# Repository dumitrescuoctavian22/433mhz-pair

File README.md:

# 433mhz-pair
A pair of transmitter and receiver with 4 channels working on 433,92Mhz

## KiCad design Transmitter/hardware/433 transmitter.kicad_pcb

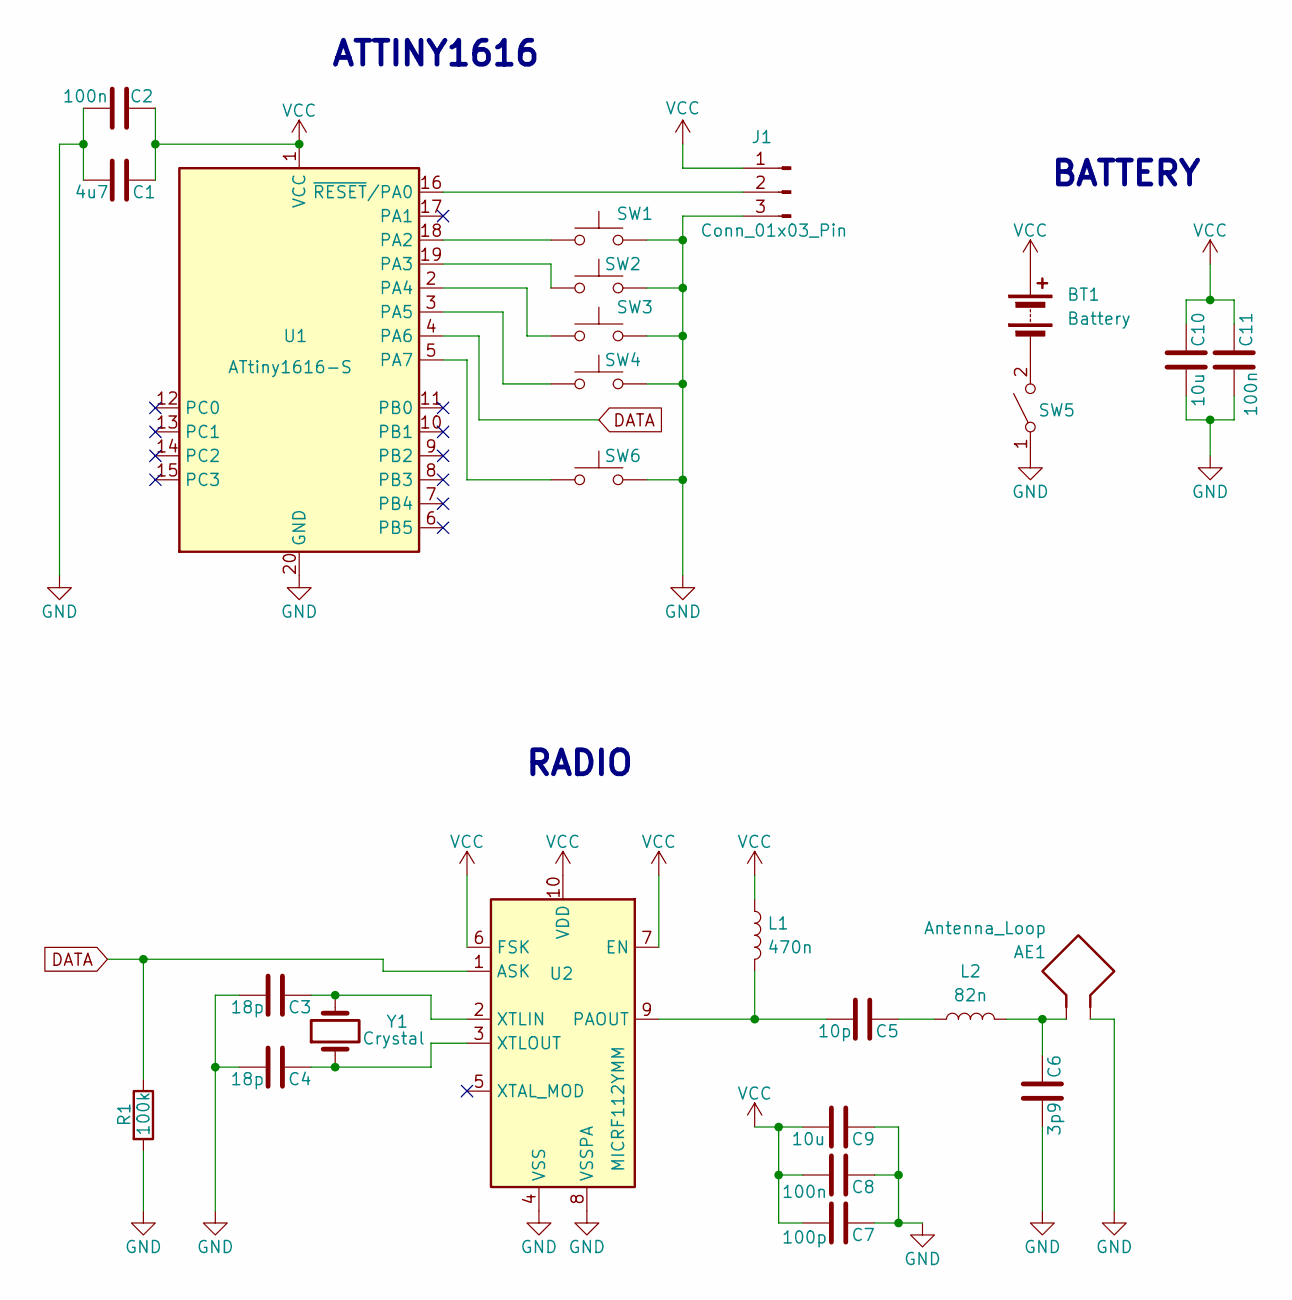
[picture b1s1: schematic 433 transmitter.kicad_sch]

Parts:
AE1: Antenna_Loop; TestPoint_2Pads_Pitch5.08mm_Drill1.3mm
BT1: Battery; TestPoint_2Pads_Pitch5.08mm_Drill1.3mm
C1: 4u7; C_0805_2012Metric_Pad1.18x1.45mm_HandSolder
C2, C8, C11: 100n; C_0805_2012Metric_Pad1.18x1.45mm_HandSolder
C3, C4: 18p; C_0603_1608Metric_Pad1.08x0.95mm_HandSolder
C5: 10p; C_0603_1608Metric_Pad1.08x0.95mm_HandSolder
C6: 3p9; C_0603_1608Metric_Pad1.08x0.95mm_HandSolder
C7: 100p; C_0805_2012Metric_Pad1.18x1.45mm_HandSolder
C9, C10: 10u; C_0805_2012Metric_Pad1.18x1.45mm_HandSolder
J1: Conn_01x03_Pin; PinHeader_1x03_P2.54mm_Vertical
L1: 470n; 470n L
L2: 82n; 82n L
R1: 100k; R_0805_2012Metric_Pad1.20x1.40mm_HandSolder
SW1, SW2, SW3, SW4, SW6: SW_Push; SW_PUSH_6mm
SW5: SW_SPST; SW_Slide_SPDT_Angled_CK_OS102011MA1Q
U1: ATtiny1616-S; SOIC-20W_7.5x12.8mm_P1.27mm
U2: MICRF112YMM; MSOP-10_3x3mm_P0.5mm
Y1: Crystal; Crystal Oscilator

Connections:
DATA: R1.1, U1.4 (PA6), U2.1 (ASK)
GND: AE1.2, C1.2, C2.2, C3.2, C4.2, C6.2, C7.1, C8.1, C9.1, C10.2, C11.2, J1.3, R1.2, SW1.2, SW2.2, SW3.2, SW4.2, SW5.1 (A), SW6.2, U1.20 (GND), U2.4 (VSS), U2.8 (VSSPA)
unnamed: AE1.1, C6.1, L2.2
unnamed: BT1.2 (-), SW5.2 (B)
unnamed: C5.1, L2.1
unnamed: J1.2, U1.16 (~RESET/PA0)
unnamed: SW1.1, U1.18 (PA2)
unnamed: SW2.1, U1.19 (PA3)
unnamed: SW3.1, U1.2 (PA4)
unnamed: SW4.1, U1.3 (PA5)
unnamed: SW6.1, U1.5 (PA7)
unnamed: C5.2, L1.2, U2.9 (PAOUT)
unnamed: C3.1, U2.2 (XTLIN), Y1.2
unnamed: C4.1, U2.3 (XTLOUT), Y1.1
VCC: BT1.1 (+), C1.1, C2.1, C7.2, C8.2, C9.2, C10.1, C11.1, J1.1, L1.1, U1.1 (VCC), U2.6 (FSK), U2.7 (EN), U2.10 (VDD)

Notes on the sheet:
RADIO
BATTERY
ATTINY1616

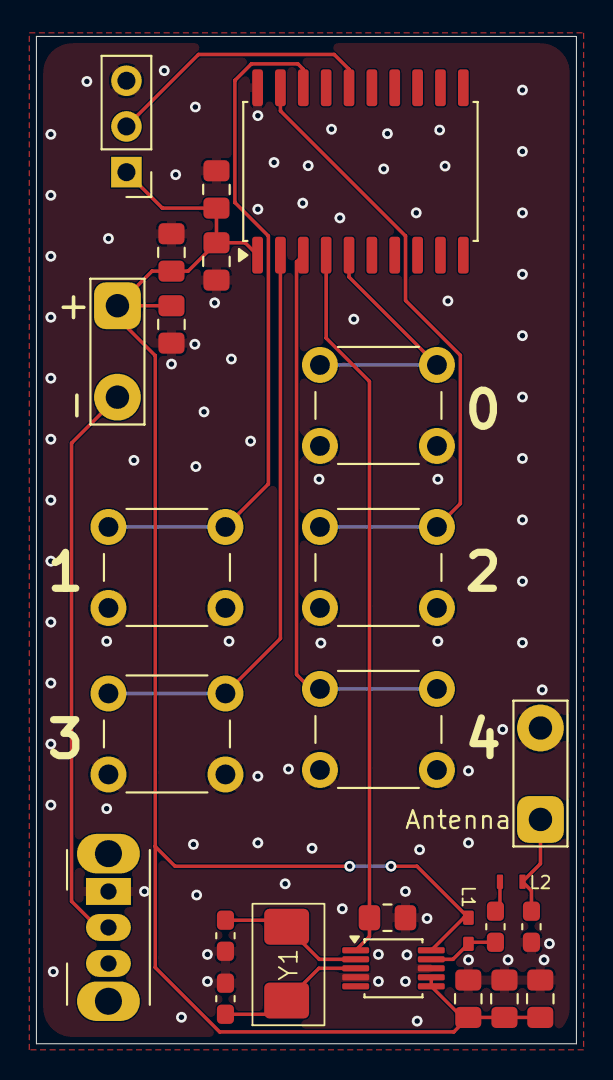
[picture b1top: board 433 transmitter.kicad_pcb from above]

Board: 2 copper layers, 30.0 x 56.0 mm, 26 parts (0 on the bottom side), 15 nets.
